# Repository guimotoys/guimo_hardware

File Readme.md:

# [Guimo&trade;] Hardware Sources

## What is Guimo&trade;?
[Guimo&trade;] is a modular smart toy, created to inspire children to live out-of-this-world experiences! It is a being from another planet, who was on an intergallactic mission when was hit by a meteor and fell on the Earth, losing parts of its pieces, programming and personality. The children's goal is to help [Guimo&trade;] recover its programming and mold its personality, by using our free app on a tablet or compatible smartphone.

## What is the [Guimo&trade;] Hardware Sources?   

Aqui na pasta de Hardware existe uma lista de todos os componentes necessários para se fazer um Guimo. Essa lista chama-se BOM-Guimo, sinta-se à vontade para baixá-la e adicionar componentes que possam ser compatíveis.

Além disso, há um arquivo com o esquemático da placa do Core. Faça o download e exporte o arquivo da PCB em PDF para posteriormente imprimí-lo e fazer sua própria placa caseira do guimo.
Abaixo segue um tutorial de como fazer sua própria PCB caseira e os materiais necessários:
http://www.robsonmartins.com/eletr/transfterm/

* Observação:
Na hora de fazer a impressão do seu PDF, deve-se atentar-se à orientação da imagem, pois a mesma deve estar invertida como um espelho do circuito final desejado.

## License
Copyright CERN 2013.

This documentation describes Open Hardware and is licensed under the CERN OHL v. 1.2.

You may redistribute and modify this documentation under the terms of the CERN OHL v.1.2. (http://ohwr.org/cernohl). This documentation is distributed WITHOUT ANY EXPRESS OR IMPLIED WARRANTY, INCLUDING OF 
MERCHANTABILITY, SATISFACTORY QUALITY AND FITNESS FOR A PARTICULAR PURPOSE. Please see the CERN OHL v.1.2 for applicable conditions

[Guimo&trade;]: <https://guimo.toys>

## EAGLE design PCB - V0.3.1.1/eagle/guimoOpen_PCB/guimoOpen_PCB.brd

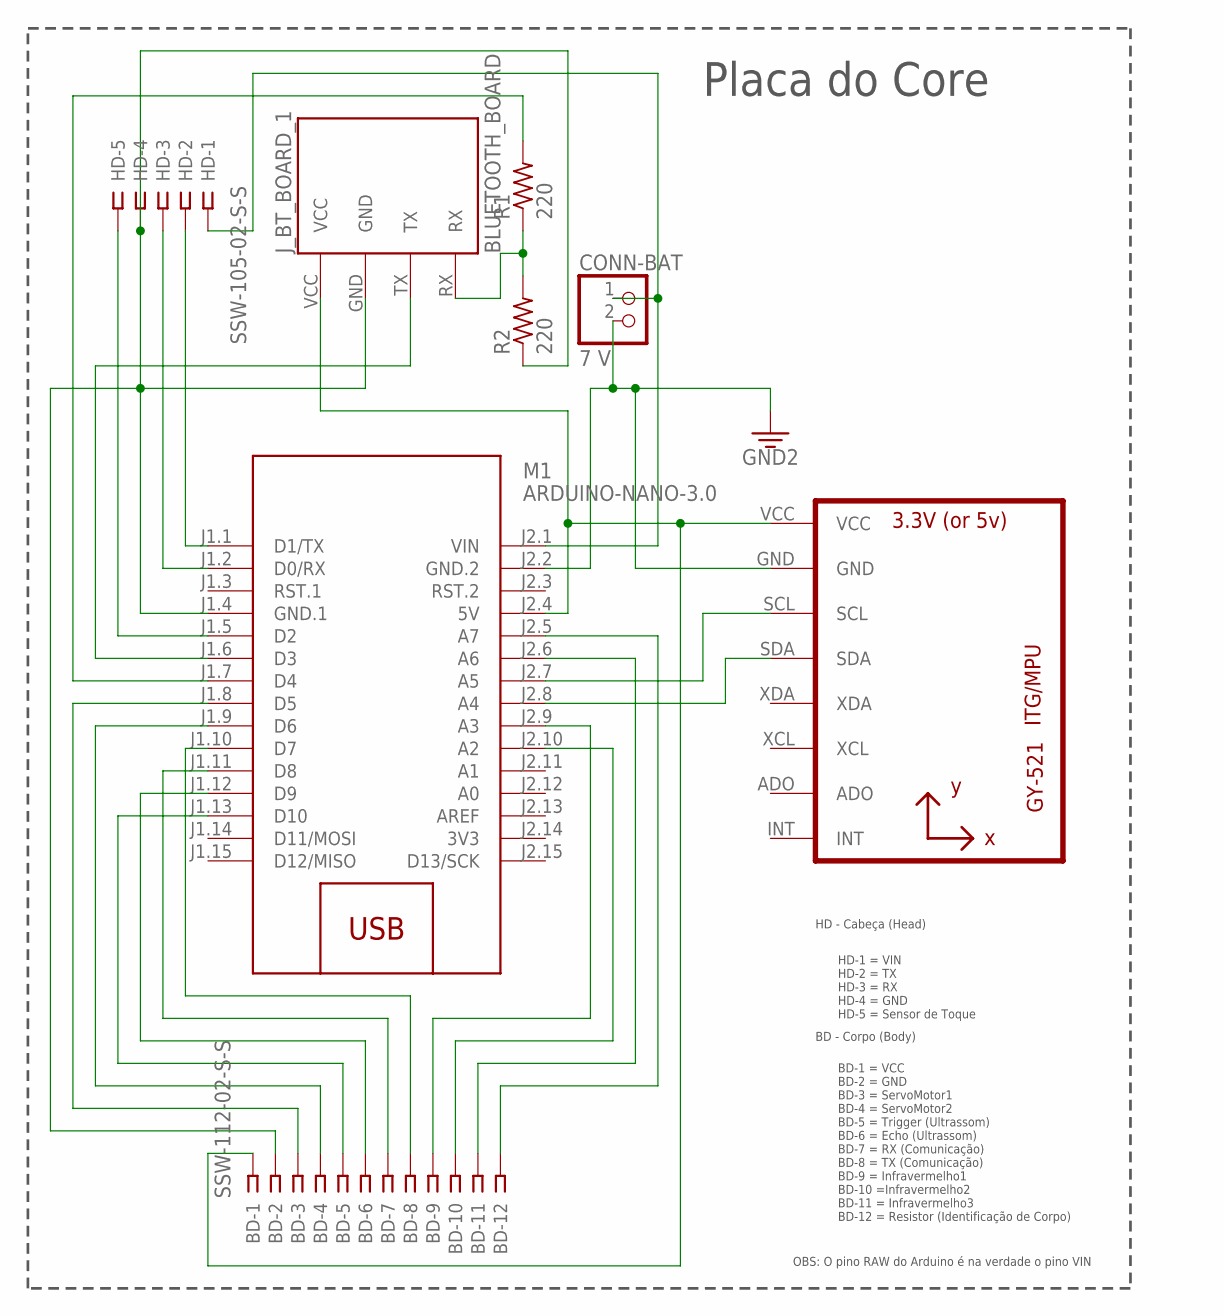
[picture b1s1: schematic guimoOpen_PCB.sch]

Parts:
BD: SSW-112-02-S-S
CONN-BAT: 7 V; 1X02
HD: SSW-105-02-S-S
J_BT_BOARD_1: BLUETOOTH_BOARD; BT_BOARD_FOOTPRINT
M1: ARDUINO-NANO-3.0
R1, R2: 220; 0207/7
U1: GY-521MPU6050; GY-521

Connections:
3V3: M1.J2.14 (3V3)
GND: BD.2, HD.4, J_BT_BOARD_1.GND, M1.J1.4 (GND.1), R2.1
GND1: CONN-BAT.2, M1.J2.2 (GND.2), U1.GND
unnamed: J_BT_BOARD_1.RX, R1.1, R2.2
unnamed: BD.1, J_BT_BOARD_1.VCC, M1.J2.4 (5V), U1.VCC
unnamed: M1.J2.7 (A5), U1.SCL
unnamed: M1.J2.8 (A4), U1.SDA
unnamed: HD.5, M1.J1.5 (D2)
unnamed: CONN-BAT.1, HD.1, M1.J2.1 (VIN)
unnamed: M1.J1.7 (D4), R1.2
unnamed: BD.4, M1.J1.9 (D6)
unnamed: BD.6, M1.J1.12 (D9)
unnamed: BD.7, M1.J1.11 (D8)
unnamed: BD.5, M1.J1.13 (D10)
unnamed: BD.3, M1.J1.8 (D5)
unnamed: BD.8, M1.J1.10 (D7)
unnamed: BD.12, M1.J2.5 (A7)
unnamed: BD.11, M1.J2.6 (A6)
unnamed: J_BT_BOARD_1.TX, M1.J1.6 (D3)
unnamed: HD.2, M1.J1.1 (D1/TX)
unnamed: BD.9, M1.J2.9 (A3)
unnamed: BD.10, M1.J2.10 (A2)
unnamed: HD.3, M1.J1.2 (D0/RX)

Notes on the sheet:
Placa do Core
BD-1 = VCC BD-2 = GND BD-3 = ServoMotor1 BD-4 = ServoMotor2 BD-5 = Trigger (Ultrassom) BD-6 = Echo (Ultrassom) BD-7 = RX (Comunicação) BD-8 = TX (Comunicação) BD-9 = Infravermelho1 BD-10 =Infravermelho2 BD-11 = Infravermelho3 BD-12 = Resistor (Identificação de Corpo)
HD-1 = VIN HD-2 = TX HD-3 = RX HD-4 = GND HD-5 = Sensor de Toque
HD - Cabeça (Head)
BD - Corpo (Body)
OBS: O pino RAW do Arduino é na verdade o pino VIN

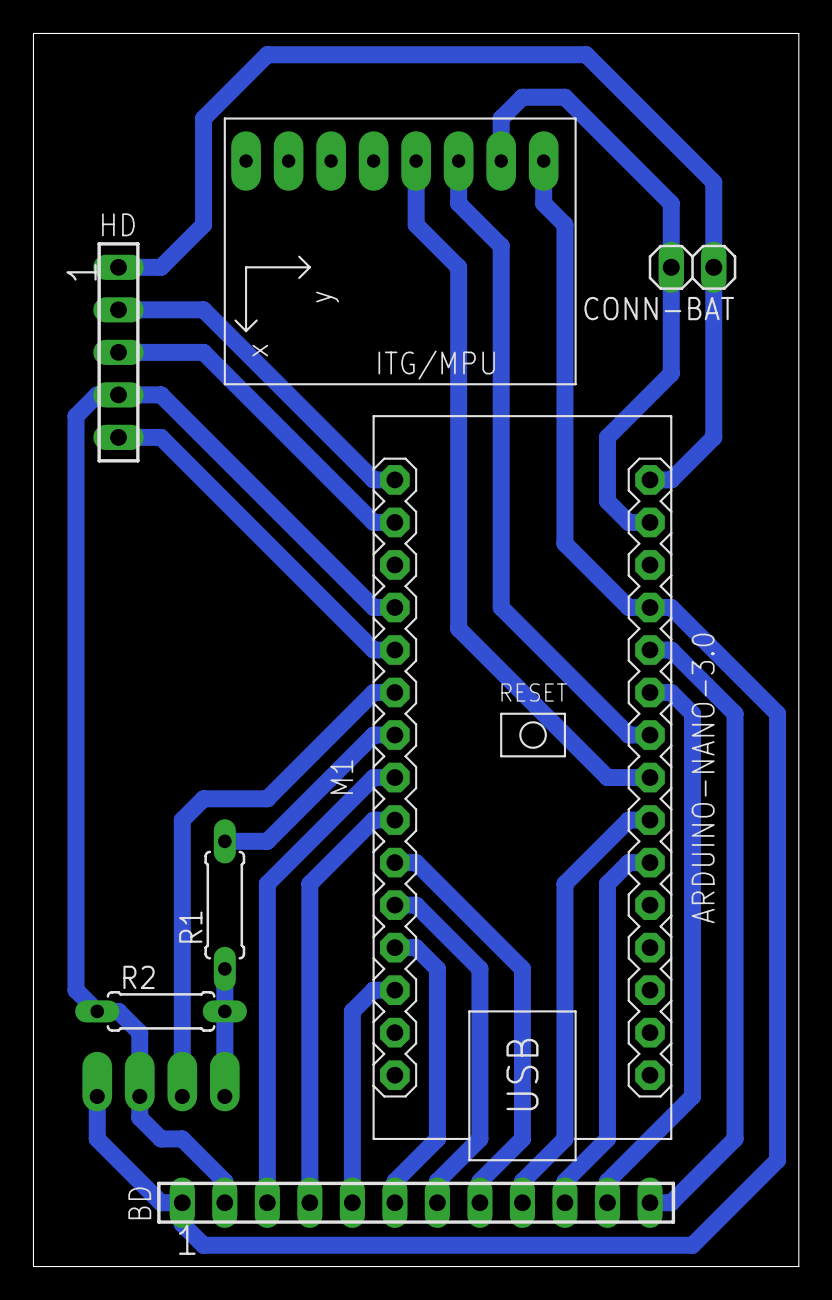
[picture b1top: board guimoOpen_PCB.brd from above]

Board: 2 copper layers, 45.7 x 73.7 mm, 8 parts (1 on the bottom side), 22 nets.

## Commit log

2017-01-29 Programas do Guimo até a entrevista pra Globo.
2017-01-29 Programas corretos do Core. Recebendo e enviando os códigos de imagem BMP
2017-01-29 Apaguei a outra versão, pois não era o programa correto e mais recente que está rodando no Guimo
2017-01-29 Acrescentei o código do acelerômetro para identificar quando o Guimo está de ponta-cabeça
2017-03-03 Correção da exibição do texto.
2017-03-03 Apagado programa desnecessário.
2017-03-03 Added Readme.md
2017-03-03 Added License.md
2017-03-03 Updated guimo readme.md
2017-03-07 Projetos da PCB Versão 0.3.1
2017-03-07 Atualização do diretório PCB
2017-03-07 Apaguei os programas da pasta guimo_hardware e os realoquei para a pasta guimo_firmware
2017-03-07 Novo layout da PCB com o programa Fritzing com alguns problemas corrigidos (divisor de tensão e alimentação 5V do corpo)
2017-03-07 Bill Of Materials do Guimo - Primeira versão
2017-03-13 Nova PCB do Guimo no software Eagle. Pendente de teste.
2017-03-19 Imagens para impressão da placa PCB corrigidas
2017-05-05 Correção do roteamento do acelerômetro. SDA e SCL foram colocadas nas portas A4 e A5

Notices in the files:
parts and their libraries:
diy-modules: Released under the Creative Commons Attribution 4.0 International License: http://creativecommons.org/licenses/by/4.0
SparkFun-PowerSymbols: Licensing: Creative Commons ShareAlike 4.0 International - https://creativecommons.org/licenses/by-sa/4.0
